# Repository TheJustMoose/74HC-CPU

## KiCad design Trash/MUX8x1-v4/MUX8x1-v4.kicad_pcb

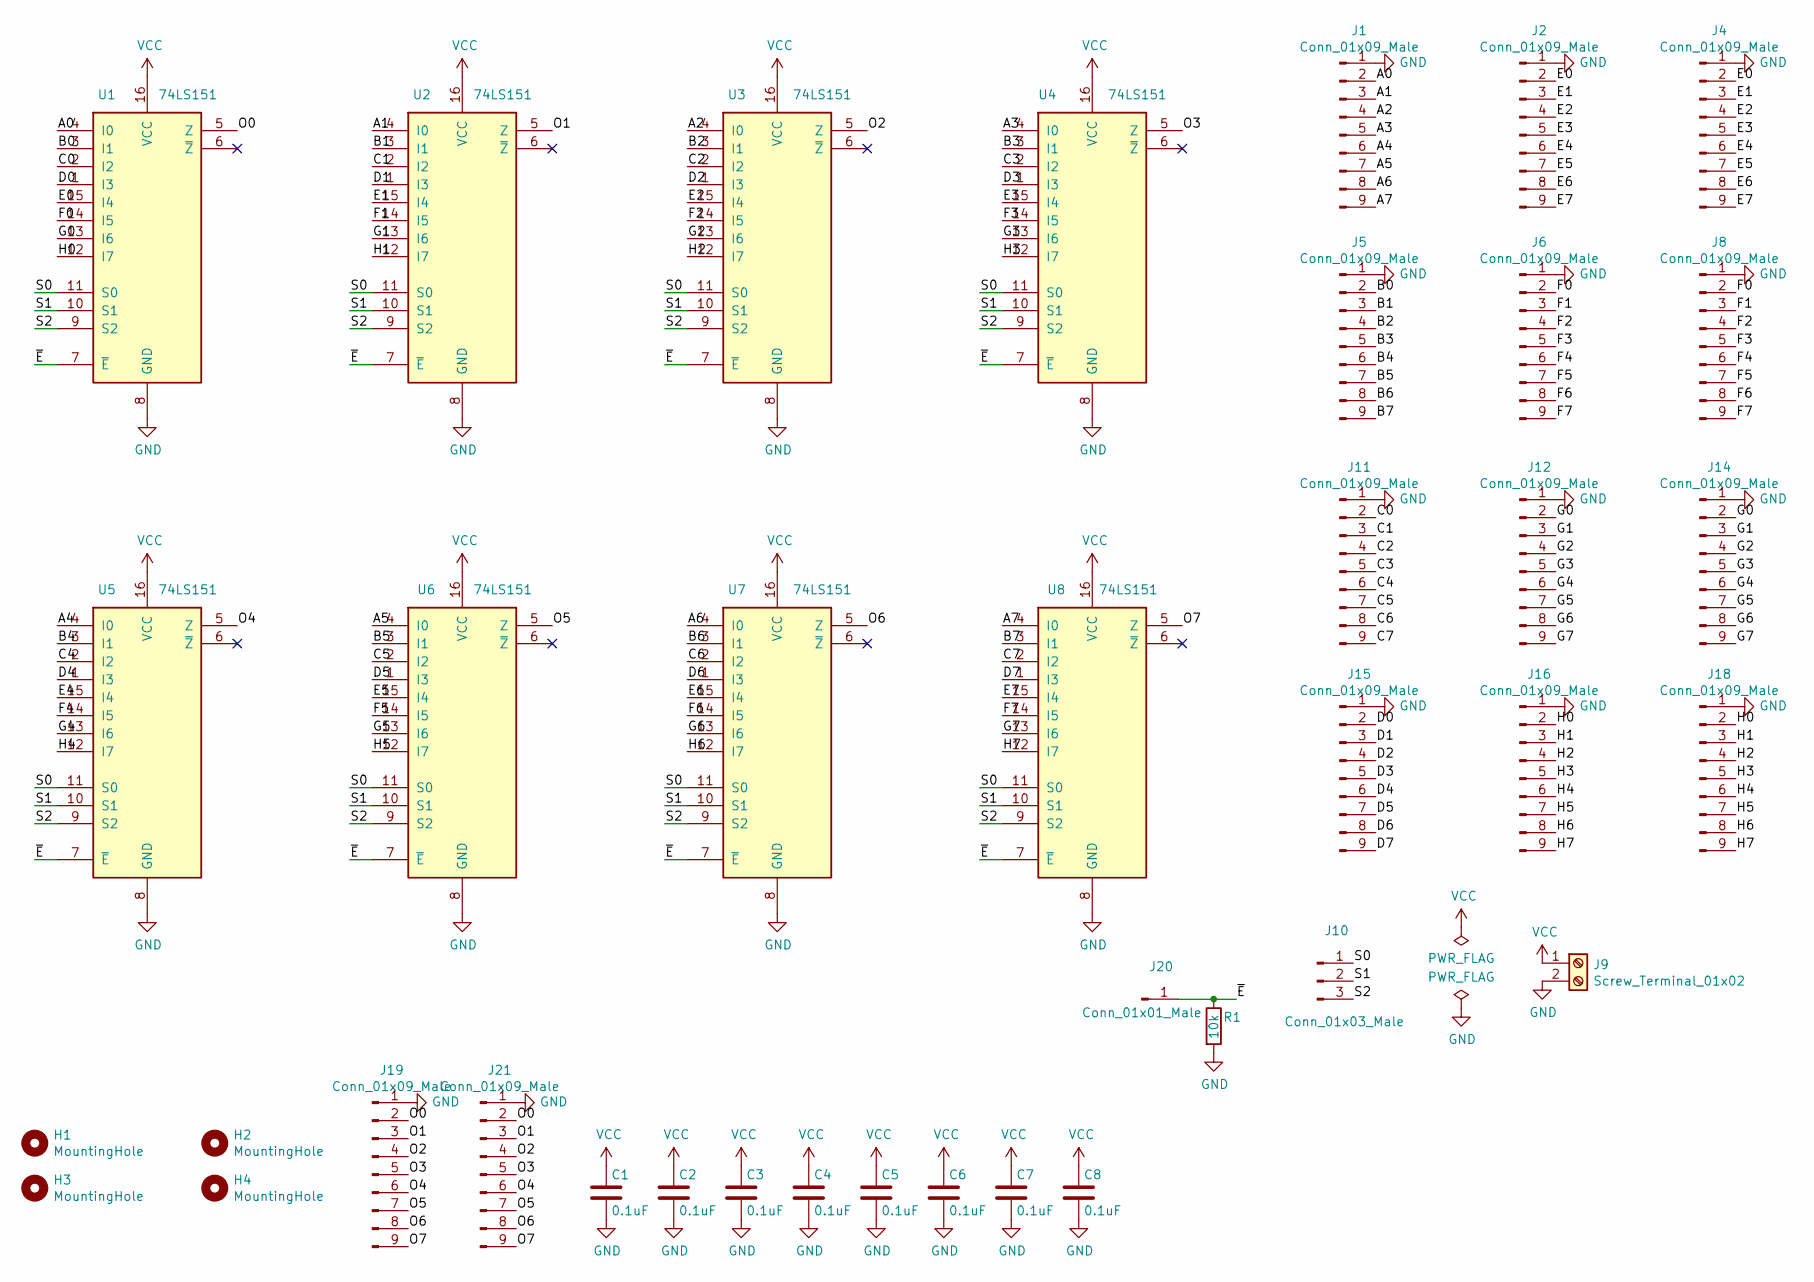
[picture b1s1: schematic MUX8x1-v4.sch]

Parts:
C1, C2, C3, C4, C5, C6, C7, C8: 0.1uF; C_Axial_L5.1mm_D3.1mm_P15.00mm_Horizontal
H1, H2, H3, H4: MountingHole; MountingHole_3.2mm_M3
J1, J2, J4, J5, J6, J8, J11, J12, J14, J15, J16, J18, J19, J21: Conn_01x09_Male; PinHeader_1x09_P2.54mm_Vertical
J9: Screw_Terminal_01x02; TerminalBlock_Phoenix_MKDS-1,5-2_1x02_P5.00mm_Horizontal
J10: Conn_01x03_Male; PinHeader_1x03_P2.54mm_Vertical
J20: Conn_01x01_Male; PinHeader_1x01_P2.54mm_Vertical
R1: 10k; R_0805_2012Metric_Pad1.20x1.40mm_HandSolder
U1, U2, U3, U4, U5, U6, U7, U8: 74LS151; DIP-16_W7.62mm_Socket

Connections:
/A0: J1.2, U1.4 (I0)
/A1: J1.3, U2.4 (I0)
/A2: J1.4, U3.4 (I0)
/A3: J1.5, U4.4 (I0)
/A4: J1.6, U5.4 (I0)
/A5: J1.7, U6.4 (I0)
/A6: J1.8, U7.4 (I0)
/A7: J1.9, U8.4 (I0)
/B0: J5.2, U1.3 (I1)
/B1: J5.3, U2.3 (I1)
/B2: J5.4, U3.3 (I1)
/B3: J5.5, U4.3 (I1)
/B4: J5.6, U5.3 (I1)
/B5: J5.7, U6.3 (I1)
/B6: J5.8, U7.3 (I1)
/B7: J5.9, U8.3 (I1)
/C0: J11.2, U1.2 (I2)
/C1: J11.3, U2.2 (I2)
/C2: J11.4, U3.2 (I2)
/C3: J11.5, U4.2 (I2)
/C4: J11.6, U5.2 (I2)
/C5: J11.7, U6.2 (I2)
/C6: J11.8, U7.2 (I2)
/C7: J11.9, U8.2 (I2)
/D0: J15.2, U1.1 (I3)
/D1: J15.3, U2.1 (I3)
/D2: J15.4, U3.1 (I3)
/D3: J15.5, U4.1 (I3)
/D4: J15.6, U5.1 (I3)
/D5: J15.7, U6.1 (I3)
/D6: J15.8, U7.1 (I3)
/D7: J15.9, U8.1 (I3)
/E0: J2.2, J4.2, U1.15 (I4)
/E1: J2.3, J4.3, U2.15 (I4)
/E2: J2.4, J4.4, U3.15 (I4)
/E3: J2.5, J4.5, U4.15 (I4)
/E4: J2.6, J4.6, U5.15 (I4)
/E5: J2.7, J4.7, U6.15 (I4)
/E6: J2.8, J4.8, U7.15 (I4)
/E7: J2.9, J4.9, U8.15 (I4)
/F0: J6.2, J8.2, U1.14 (I5)
/F1: J6.3, J8.3, U2.14 (I5)
/F2: J6.4, J8.4, U3.14 (I5)
/F3: J6.5, J8.5, U4.14 (I5)
/F4: J6.6, J8.6, U5.14 (I5)
/F5: J6.7, J8.7, U6.14 (I5)
/F6: J6.8, J8.8, U7.14 (I5)
/F7: J6.9, J8.9, U8.14 (I5)
/G0: J12.2, J14.2, U1.13 (I6)
/G1: J12.3, J14.3, U2.13 (I6)
/G2: J12.4, J14.4, U3.13 (I6)
/G3: J12.5, J14.5, U4.13 (I6)
/G4: J12.6, J14.6, U5.13 (I6)
/G5: J12.7, J14.7, U6.13 (I6)
/G6: J12.8, J14.8, U7.13 (I6)
/G7: J12.9, J14.9, U8.13 (I6)
/H0: J16.2, J18.2, U1.12 (I7)
/H1: J16.3, J18.3, U2.12 (I7)
/H2: J16.4, J18.4, U3.12 (I7)
/H3: J16.5, J18.5, U4.12 (I7)
/H4: J16.6, J18.6, U5.12 (I7)
/H5: J16.7, J18.7, U6.12 (I7)
/H6: J16.8, J18.8, U7.12 (I7)
/H7: J16.9, J18.9, U8.12 (I7)
/O0: J19.2, J21.2, U1.5 (Z)
/O1: J19.3, J21.3, U2.5 (Z)
/O2: J19.4, J21.4, U3.5 (Z)
/O3: J19.5, J21.5, U4.5 (Z)
/O4: J19.6, J21.6, U5.5 (Z)
/O5: J19.7, J21.7, U6.5 (Z)
/O6: J19.8, J21.8, U7.5 (Z)
/O7: J19.9, J21.9, U8.5 (Z)
/S0: J10.1, U1.11 (S0), U2.11 (S0), U3.11 (S0), U4.11 (S0), U5.11 (S0), U6.11 (S0), U7.11 (S0), U8.11 (S0)
/S1: J10.2, U1.10 (S1), U2.10 (S1), U3.10 (S1), U4.10 (S1), U5.10 (S1), U6.10 (S1), U7.10 (S1), U8.10 (S1)
/S2: J10.3, U1.9 (S2), U2.9 (S2), U3.9 (S2), U4.9 (S2), U5.9 (S2), U6.9 (S2), U7.9 (S2), U8.9 (S2)
/~E: J20.1, R1.1, U1.7 (~E), U2.7 (~E), U3.7 (~E), U4.7 (~E), U5.7 (~E), U6.7 (~E), U7.7 (~E), U8.7 (~E)
GND: C1.2, C2.2, C3.2, C4.2, C5.2, C6.2, C7.2, C8.2, J1.1, J2.1, J4.1, J5.1, J6.1, J8.1, J9.2, J11.1, J12.1, J14.1, J15.1, J16.1, J18.1, J19.1, J21.1, R1.2, U1.8 (GND), U2.8 (GND), U3.8 (GND), U4.8 (GND), U5.8 (GND), U6.8 (GND), U7.8 (GND), U8.8 (GND)
VCC: C1.1, C2.1, C3.1, C4.1, C5.1, C6.1, C7.1, C8.1, J9.1, U1.16 (VCC), U2.16 (VCC), U3.16 (VCC), U4.16 (VCC), U5.16 (VCC), U6.16 (VCC), U7.16 (VCC), U8.16 (VCC)

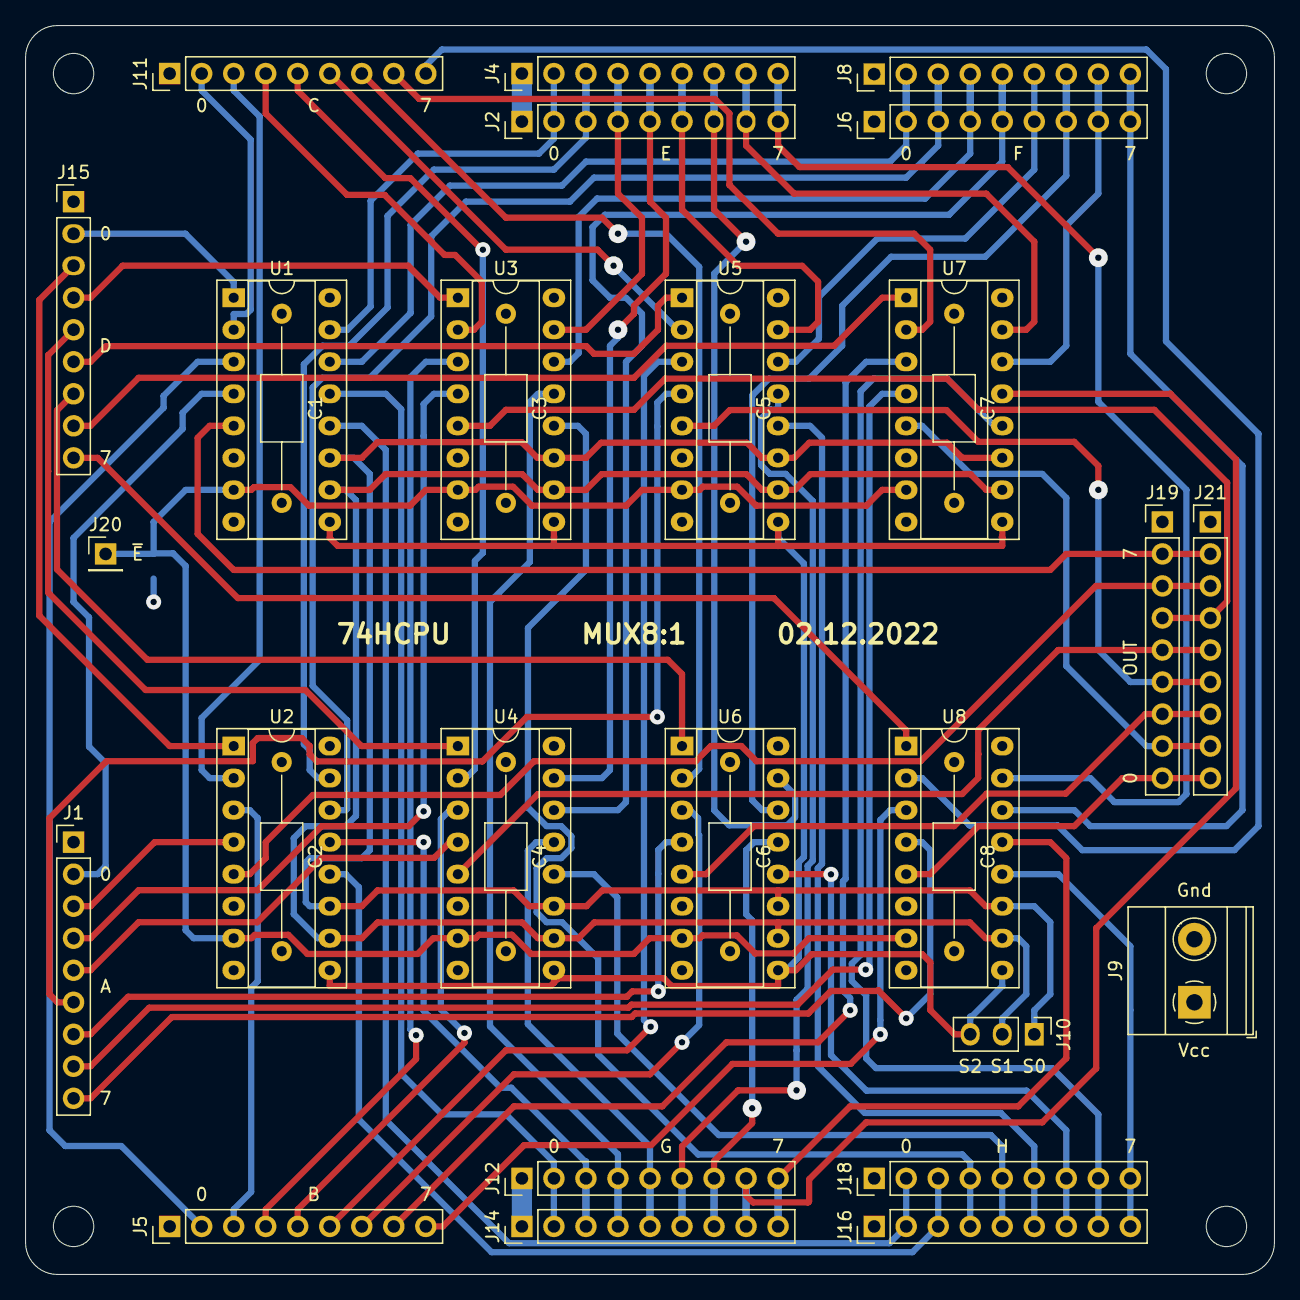
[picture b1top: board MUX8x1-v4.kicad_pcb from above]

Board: 4 copper layers, 99.1 x 99.1 mm, 38 parts (1 on the bottom side), 78 nets.

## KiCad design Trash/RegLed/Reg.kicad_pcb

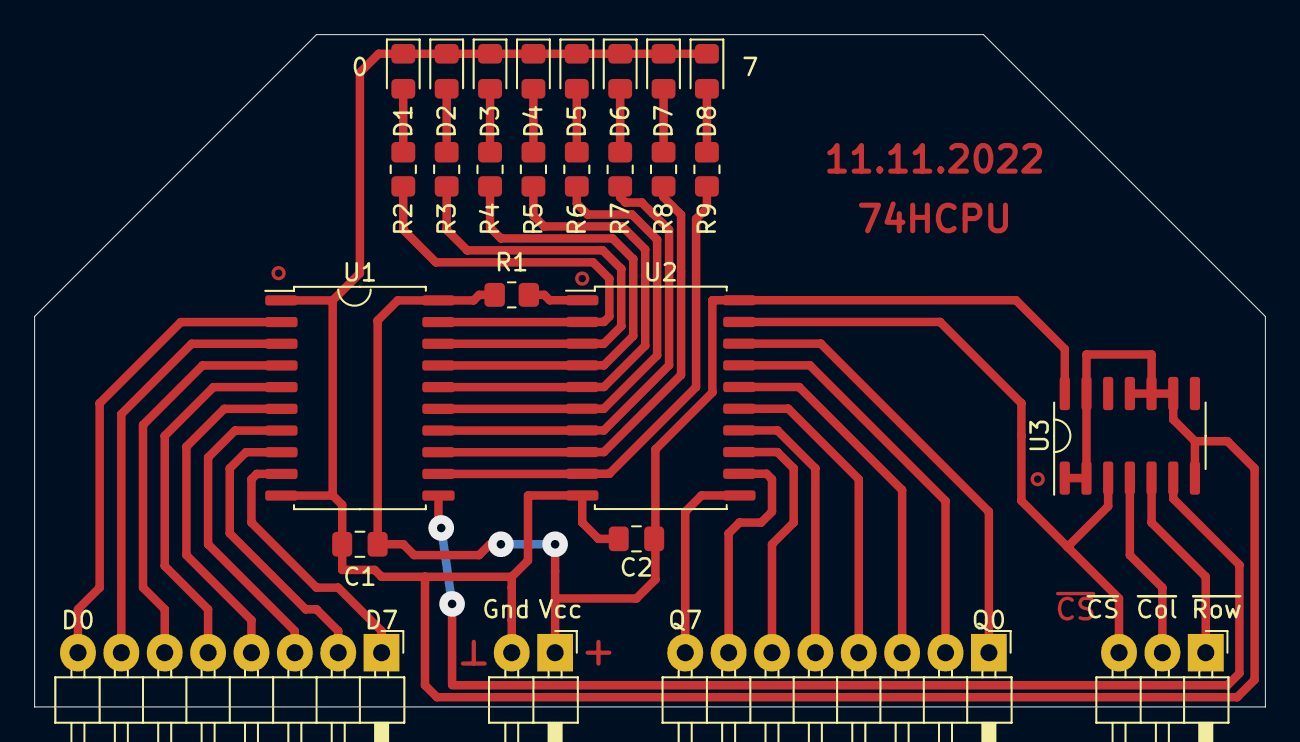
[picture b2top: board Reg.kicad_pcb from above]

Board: 2 copper layers, 72.1 x 39.4 mm, 26 parts (0 on the bottom side), 39 nets.

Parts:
C1, C2: 0.1uF; C_0805_2012Metric_Pad1.18x1.45mm_HandSolder
D1, D2, D3, D4, D5, D6, D7, D8: LED; LED_0805_2012Metric_Pad1.15x1.40mm_HandSolder
J1, J2: Conn_01x08_Male; PinHeader_1x08_P2.54mm_Horizontal
J3: Conn_01x02_Male; PinHeader_1x02_P2.54mm_Horizontal
J4: Conn_01x03_Male; PinHeader_1x03_P2.54mm_Horizontal
R1: 10k; R_0805_2012Metric_Pad1.20x1.40mm_HandSolder
R2, R3, R4, R5, R6, R7, R8, R9: 1k; R_0805_2012Metric_Pad1.20x1.40mm_HandSolder
U1: 74LS573; SOP-20_7.5x12.8mm_P1.27mm
U2: 74HC245; SOP-20_7.5x12.8mm_P1.27mm
U3: 74LS27; SO-14_3.9x8.65mm_P1.27mm

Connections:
/D0: J1.8, U1.2
/D1: J1.7, U1.3
/D2: J1.6, U1.4
/D3: J1.5, U1.5
/D4: J1.4, U1.6
/D5: J1.3, U1.7
/D6: J1.2, U1.8
/D7: J1.1, U1.9
/L0: R2.1, U1.19, U2.2
/L1: R3.1, U1.18, U2.3
/L2: R4.1, U1.17, U2.4
/L3: R5.1, U1.16, U2.5
/L4: R6.1, U1.15, U2.6
/L5: R7.1, U1.14, U2.7
/L6: R8.1, U1.13, U2.8
/L7: R9.1, U1.12, U2.9
/Q0: J2.1, U2.18
/Q1: J2.2, U2.17
/Q2: J2.3, U2.16
/Q3: J2.4, U2.15
/Q4: J2.5, U2.14
/Q5: J2.6, U2.13
/Q6: J2.7, U2.12
/Q7: J2.8, U2.11
/~CS: J4.3, U2.19, U3.3
/~Col: J4.2, U3.4
/~Row: J4.1, U3.5
GND: C1.2, C2.2, D1.1, D2.1, D3.1, D4.1, D5.1, D6.1, D7.1, D8.1, J3.2, U1.1, U1.10, U2.10, U3.1, U3.2, U3.7, U3.9, U3.10, U3.11, U3.13
unnamed: D1.2, R2.2
unnamed: D2.2, R3.2
unnamed: D3.2, R4.2
unnamed: D4.2, R5.2
unnamed: D5.2, R6.2
unnamed: D6.2, R7.2
unnamed: D7.2, R8.2
unnamed: D8.2, R9.2
unnamed: R1.1, U2.1
unnamed: U1.11, U3.6
VCC: C1.1, C2.1, J3.1, R1.2, U1.20, U2.20, U3.14

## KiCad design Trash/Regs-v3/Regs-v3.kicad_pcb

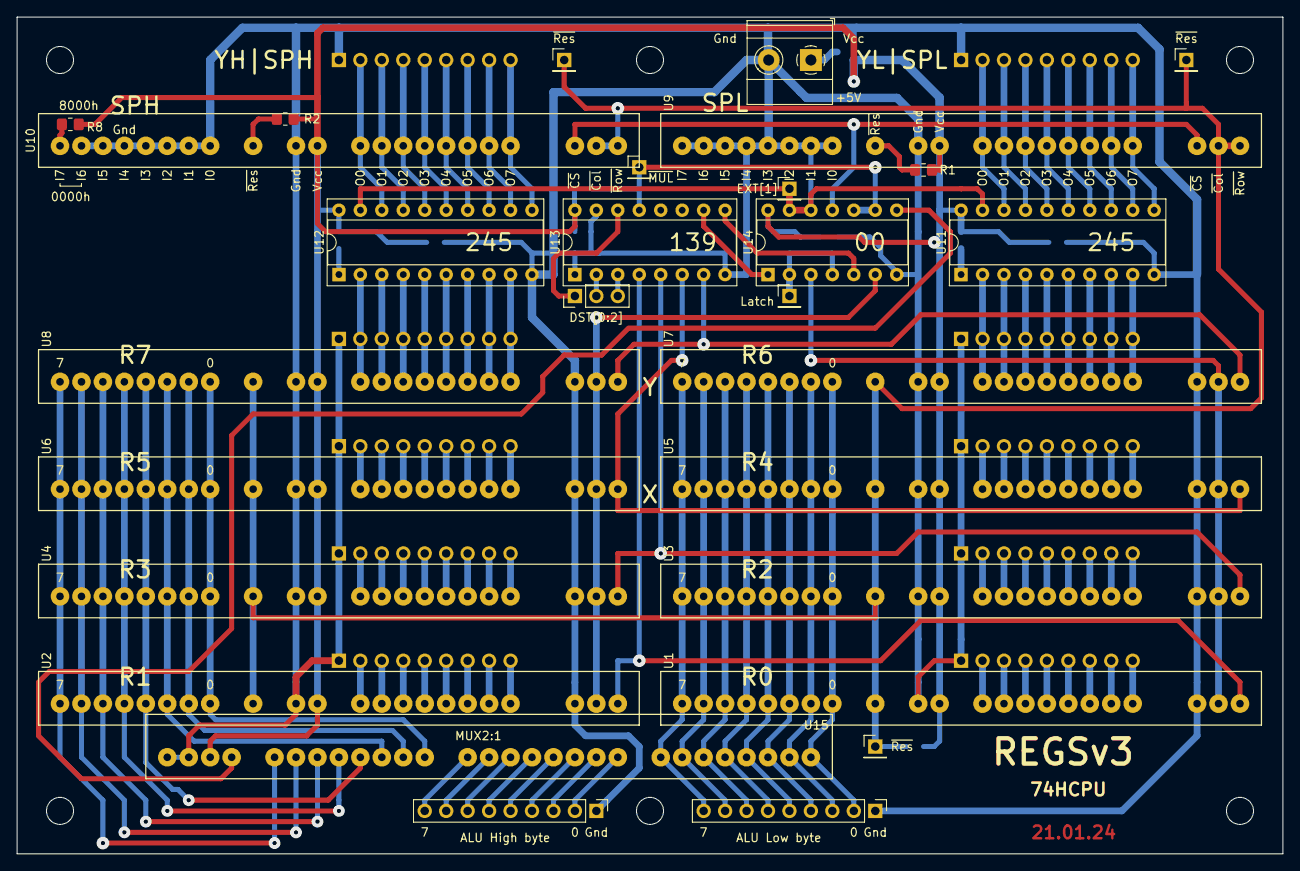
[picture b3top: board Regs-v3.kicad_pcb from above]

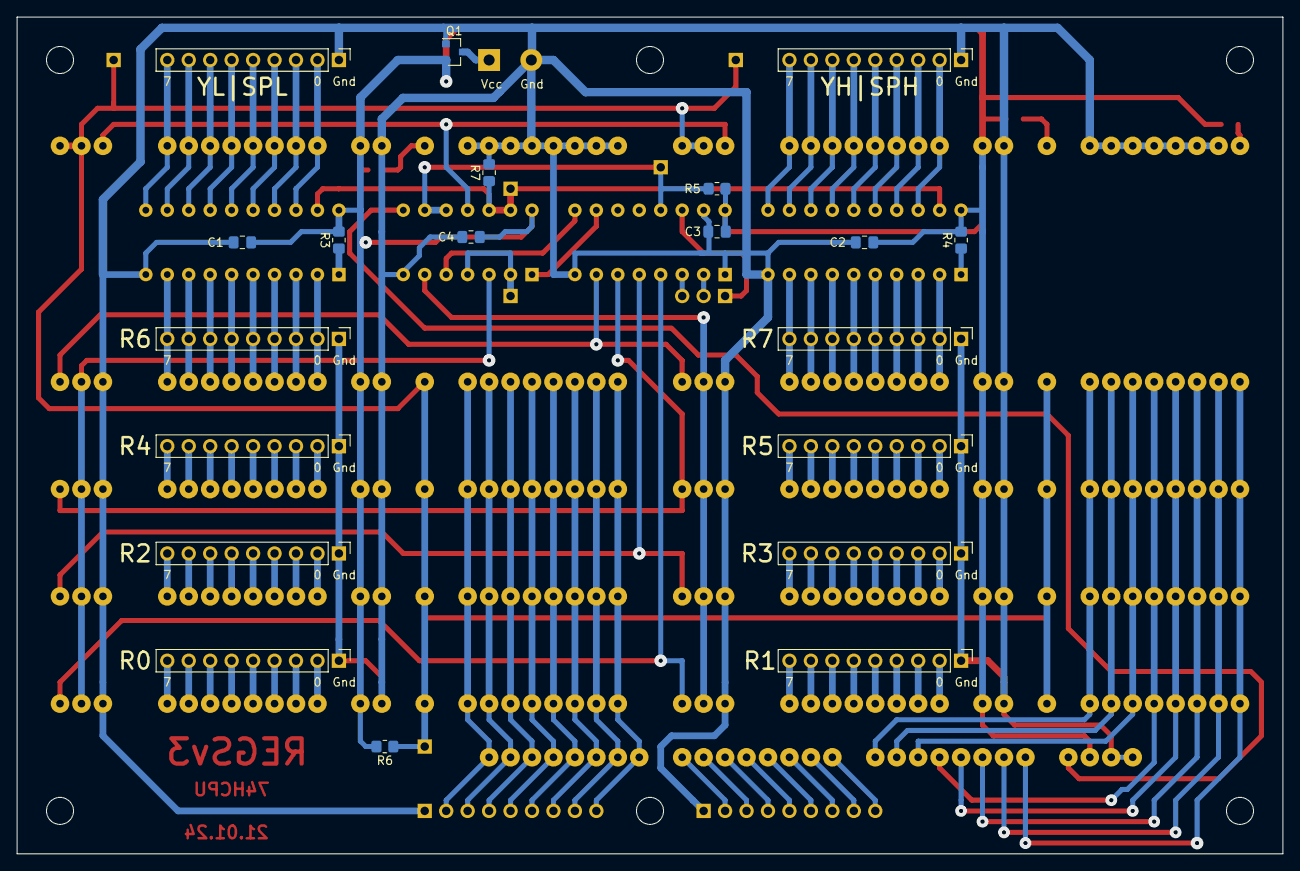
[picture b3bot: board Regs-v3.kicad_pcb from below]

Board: 2 copper layers, 149.9 x 99.1 mm, 54 parts (20 on the bottom side), 129 nets.

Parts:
C1, C2, C3, C4: 0.1uF; C_0805_2012Metric_Pad1.18x1.45mm_HandSolder
H1, H2, H3, H4, H5, H6: MountingHole; MountingHole_3.2mm_M3
J1, J2, J3, J4, J5, J6, J7, J8, J9, J10, J17, J18: Conn_01x09_Male; PinHeader_1x09_P2.54mm_Vertical
J11: Conn_01x03_Male; PinHeader_1x03_P2.54mm_Vertical
J12, J13, J14, J15, J19, J20: Conn_01x01_Male; PinHeader_1x01_P2.54mm_Vertical
J16: Screw_Terminal_01x02; TerminalBlock_Phoenix_MKDS-1,5-2_1x02_P5.00mm_Horizontal
Q1: IRLML5203; SOT-23
R1, R2, R3, R4, R5, R6, R7, R8: 10k; R_0805_2012Metric_Pad1.20x1.40mm_HandSolder
U1, U2, U3, U4, U5, U6, U7, U8, U9, U10: REG_CNT
U11, U12: 74HC245; DIP-20_W7.62mm_Socket
U13: 74LS139; DIP-16_W7.62mm_Socket
U14: 74HC00; DIP-14_W7.62mm_Socket
U15: MUX2-1; CMDwoC

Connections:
/ALU_H0: J18.2, U15.9
/ALU_H7: J18.9, U15.16
/DST[0]: J11.1, U13.14
/DST[1]: J11.2, U13.2
/DST[2]: J11.3, U13.3
/EXT[1]: J14.1, R7.1, U11.19, U12.19, U14.12, U14.13
/H0: U2.8, U4.8, U6.8, U8.8, U15.17
/H1: U2.7, U4.7, U6.7, U8.7, U15.18
/H2: U2.6, U4.6, U6.6, U8.6, U15.19
/H3: U2.5, U4.5, U6.5, U8.5, U15.20
/H4: U2.4, U4.4, U6.4, U8.4, U15.21
/H5: U2.3, U4.3, U6.3, U8.3, U15.22
/H6: U2.2, U4.2, U6.2, U8.2, U15.23
/H7: U2.1, U4.1, U6.1, U8.1, U15.24
/L0: J17.2, U1.8, U3.8, U5.8, U7.8, U15.1
/L1: J17.3, U1.7, U3.7, U5.7, U7.7, U15.2
/L2: J17.4, U1.6, U3.6, U5.6, U7.6, U15.3
/L3: J17.5, U1.5, U3.5, U5.5, U7.5, U15.4
/L4: J17.6, U1.4, U3.4, U5.4, U7.4, U15.5
/L5: J17.7, U1.3, U3.3, U5.3, U7.3, U15.6
/L6: J17.8, U1.2, U3.2, U5.2, U7.2, U15.7
/L7: J17.9, U1.1, U3.1, U5.1, U7.1, U15.8
/Latch: J15.1, U14.2, U14.4
/R0.0: J1.2, U1.12
/R0.1: J1.3, U1.13
/R0.2: J1.4, U1.14
/R0.3: J1.5, U1.15
/R0.4: J1.6, U1.16
/R0.5: J1.7, U1.17
/R0.6: J1.8, U1.18
/R0.7: J1.9, U1.19
/R1.0: J2.2, U2.12
/R1.1: J2.3, U2.13
/R1.2: J2.4, U2.14
/R1.3: J2.5, U2.15
/R1.4: J2.6, U2.16
/R1.5: J2.7, U2.17
/R1.6: J2.8, U2.18
/R1.7: J2.9, U2.19
/R2.0: J3.2, U3.12
/R2.1: J3.3, U3.13
/R2.2: J3.4, U3.14
/R2.3: J3.5, U3.15
/R2.4: J3.6, U3.16
/R2.5: J3.7, U3.17
/R2.6: J3.8, U3.18
/R2.7: J3.9, U3.19
/R3.0: J4.2, U4.12
/R3.1: J4.3, U4.13
/R3.2: J4.4, U4.14
/R3.3: J4.5, U4.15
/R3.4: J4.6, U4.16
/R3.5: J4.7, U4.17
/R3.6: J4.8, U4.18
/R3.7: J4.9, U4.19
/R4.0: J5.2, U5.12
/R4.1: J5.3, U5.13
/R4.2: J5.4, U5.14
/R4.3: J5.5, U5.15
/R4.4: J5.6, U5.16
/R4.5: J5.7, U5.17
/R4.6: J5.8, U5.18
/R4.7: J5.9, U5.19
/R5.0: J6.2, U6.12
/R5.1: J6.3, U6.13
/R5.2: J6.4, U6.14
/R5.3: J6.5, U6.15
/R5.4: J6.6, U6.16
/R5.5: J6.7, U6.17
/R5.6: J6.8, U6.18
/R5.7: J6.9, U6.19
/R6.0: J7.2, U7.12, U11.2
/R6.1: J7.3, U7.13, U11.3
/R6.2: J7.4, U7.14, U11.4
/R6.3: J7.5, U7.15, U11.5
/R6.4: J7.6, U7.16, U11.6
/R6.5: J7.7, U7.17, U11.7
/R6.6: J7.8, U7.18, U11.8
/R6.7: J7.9, U7.19, U11.9
/R7.0: J8.2, U8.12, U12.2
/R7.1: J8.3, U8.13, U12.3
/R7.2: J8.4, U8.14, U12.4
/R7.3: J8.5, U8.15, U12.5
/R7.4: J8.6, U8.16, U12.6
/R7.5: J8.7, U8.17, U12.7
/R7.6: J8.8, U8.18, U12.8
/R7.7: J8.9, U8.19, U12.9
/YH|SPH.0: J10.2, U10.12, U12.18
/YH|SPH.1: J10.3, U10.13, U12.17
/YH|SPH.2: J10.4, U10.14, U12.16
/YH|SPH.3: J10.5, U10.15, U12.15
/YH|SPH.4: J10.6, U10.16, U12.14
/YH|SPH.5: J10.7, U10.17, U12.13
/YH|SPH.6: J10.8, U10.18, U12.12
/YH|SPH.7: J10.9, U10.19, U12.11
/YL|SPL.0: J9.2, U9.12, U11.18
/YL|SPL.1: J9.3, U9.13, U11.17
/YL|SPL.2: J9.4, U9.14, U11.16
/YL|SPL.3: J9.5, U9.15, U11.15
/YL|SPL.4: J9.6, U9.16, U11.14
/YL|SPL.5: J9.7, U9.17, U11.13
/YL|SPL.6: J9.8, U9.18, U11.12
/YL|SPL.7: J9.9, U9.19, U11.11
/~H: U2.21, U4.21, U6.21, U8.21, U14.6
/~L: U1.21, U3.21, U5.21, U7.21, U14.3
/~MUL: J12.1, R5.1, U13.13, U14.9, U14.10
/~R0: U1.22, U2.22, U13.4
/~R1: U3.22, U4.22, U13.5
/~R2: U5.22, U6.22, U13.6
/~R3: U7.22, U8.22, U13.7
/~Res: J13.1, J19.1, J20.1, R6.1, U1.9, U2.9, U3.9, U4.9, U5.9, U6.9, U7.9, U8.9, U9.21, U9.22, U10.21, U10.22
GND: C1.2, C2.2, C3.2, C4.2, J1.1, J2.1, J3.1, J4.1, J5.1, J6.1, J7.1, J8.1, J9.1, J10.1, J16.2, J17.1, J18.1, Q1.1, R7.2, U1.10, U1.20, U2.10, U2.20, U3.10, U3.20, U4.10, U4.20, U5.10, U5.20, U6.10, U6.20, U7.10, U7.20, U8.10, U8.20, U9.1, U9.2, U9.3, U9.4, U9.5, U9.6, U9.7, U9.8, U9.10, U10.2, U10.3, U10.4, U10.5, U10.6, U10.7, U10.8, U10.10, U11.10, U12.10, U13.1, U13.8, U13.15, U14.7, U15.27, U15.28
unnamed: J16.1, Q1.3
unnamed: J18.3, U15.10
unnamed: J18.4, U15.11
unnamed: J18.5, U15.12
unnamed: J18.6, U15.13
unnamed: J18.7, U15.14
unnamed: J18.8, U15.15
unnamed: R1.1, U9.9
unnamed: R2.1, U10.9
unnamed: R3.1, U11.1
unnamed: R4.1, U12.1
unnamed: R8.1, U10.1
unnamed: U9.20, U10.20, U14.11
unnamed: U13.9, U14.5
unnamed: U13.10, U14.1
unnamed: U14.8, U15.25
VCC: C1.1, C2.1, C3.1, C4.1, Q1.2, R1.2, R2.2, R3.2, R4.2, R5.2, R6.2, R8.2, U1.11, U2.11, U3.11, U4.11, U5.11, U6.11, U7.11, U8.11, U9.11, U10.11, U11.20, U12.20, U13.16, U14.14, U15.26

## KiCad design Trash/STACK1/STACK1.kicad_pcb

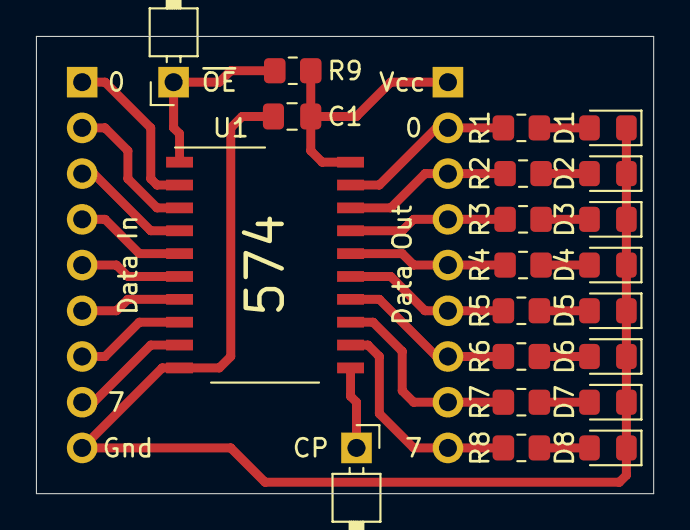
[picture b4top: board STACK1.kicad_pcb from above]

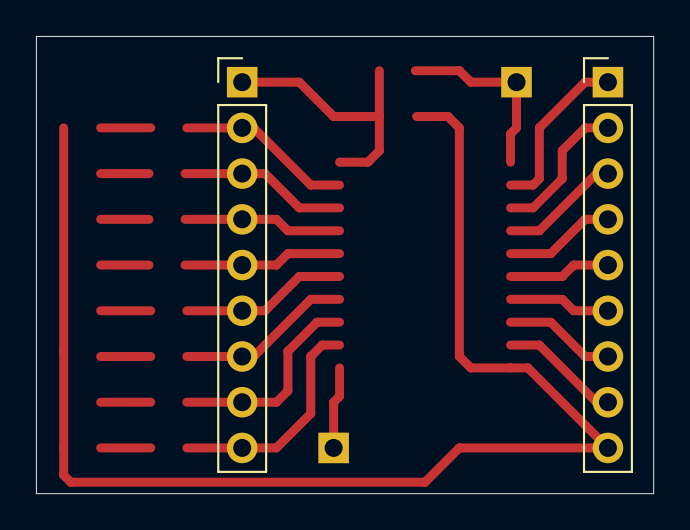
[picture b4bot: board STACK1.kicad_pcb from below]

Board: 2 copper layers, 34.3 x 25.4 mm, 23 parts (2 on the bottom side), 28 nets.

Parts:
C1: 0.1uF; C_0805_2012Metric_Pad1.18x1.45mm_HandSolder
D1, D2, D3, D4, D5, D6, D7, D8: LED; LED_0805_2012Metric_Pad1.15x1.40mm_HandSolder
J1, J2: Conn_01x09_Male; PinHeader_1x09_P2.54mm_Vertical
J3, J4: Conn_01x01_Male; PinHeader_1x01_P2.54mm_Horizontal
R1, R2, R3, R4, R5, R6, R7, R8: 1k; R_0805_2012Metric_Pad1.20x1.40mm_HandSolder
R9: 10k; R_0805_2012Metric_Pad1.20x1.40mm_HandSolder
U1: 74LS574; SO-20_12.8x7.5mm_P1.27mm

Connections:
/CP: J3.1, U1.11
/D0: J2.1, U1.2
/D7: J2.8, U1.9
/Q0: J1.2, R1.2, U1.19
/Q1: J1.3, R2.2, U1.18
/Q2: J1.4, R3.2, U1.17
/Q3: J1.5, R4.2, U1.16
/Q4: J1.6, R5.2, U1.15
/Q5: J1.7, R6.2, U1.14
/Q6: J1.8, R7.2, U1.13
/Q7: J1.9, R8.2, U1.12
/~OE: J4.1, R9.1, U1.1
GND: C1.2, D1.1, D2.1, D3.1, D4.1, D5.1, D6.1, D7.1, D8.1, J2.9, U1.10
unnamed: D1.2, R1.1
unnamed: D2.2, R2.1
unnamed: D3.2, R3.1
unnamed: D4.2, R4.1
unnamed: D5.2, R5.1
unnamed: D6.2, R6.1
unnamed: D7.2, R7.1
unnamed: D8.2, R8.1
unnamed: J2.2, U1.3
unnamed: J2.3, U1.4
unnamed: J2.4, U1.5
unnamed: J2.5, U1.6
unnamed: J2.6, U1.7
unnamed: J2.7, U1.8
VCC: C1.1, J1.1, R9.2, U1.20

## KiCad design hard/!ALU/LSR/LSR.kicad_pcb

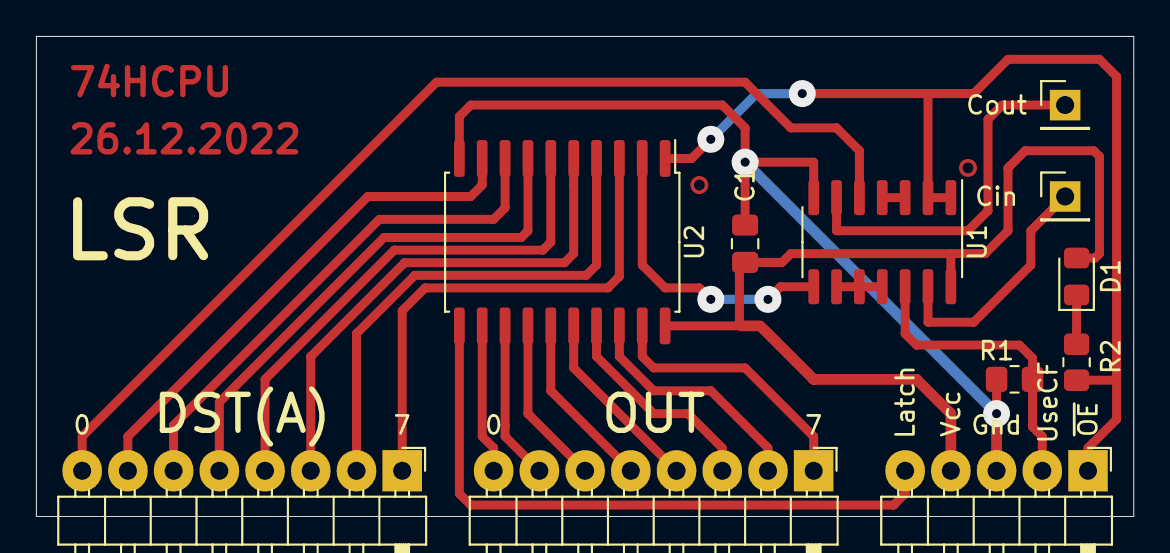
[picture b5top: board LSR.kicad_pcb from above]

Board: 2 copper layers, 61.0 x 26.7 mm, 11 parts (0 on the bottom side), 27 nets.

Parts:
C1: 0.1uF; C_0805_2012Metric_Pad1.18x1.45mm_HandSolder
D1: LED; LED_0805_2012Metric_Pad1.15x1.40mm_HandSolder
J1, J4: Conn_01x01_Male; PinHeader_1x01_P2.54mm_Vertical
J2, J3: Conn_01x08_Male; PinHeader_1x08_P2.54mm_Horizontal
J5: Conn_01x05_Male; PinHeader_1x05_P2.54mm_Horizontal
R1, R2: R; R_0805_2012Metric_Pad1.20x1.40mm_HandSolder
U1: 74HC00; SO-14_3.9x8.65mm_P1.27mm
U2: 74LS573; SOIC-20W_7.5x12.8mm_P1.27mm

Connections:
/CF_IN: J4.1, U1.13
/D0: J2.8, U1.5
/D1: J2.7, U2.9
/D2: J2.6, U2.8
/D3: J2.5, U2.7
/D4: J2.4, U2.6
/D5: J2.3, U2.5
/D6: J2.2, U2.4
/D7: J2.1, U2.3
/Latch: J5.5, U2.11
/O0: J3.8, U2.12
/O1: J3.7, U2.13
/O2: J3.6, U2.14
/O3: J3.5, U2.15
/O4: J3.4, U2.16
/O5: J3.3, U2.17
/O6: J3.2, U2.18
/O7: J3.1, U2.19
/UseCF: J5.2, R1.1, U1.12
/~(CF&OE): J1.1, U1.6
/~OE: J5.1, R2.2, U1.1, U1.2, U2.1
GND: C1.2, J5.3, R1.2, U1.7, U2.10
unnamed: D1.1, R2.1
unnamed: U1.3, U1.4
unnamed: U1.8, U2.2
unnamed: U1.9, U1.10, U1.11
VCC: C1.1, D1.2, J5.4, U1.14, U2.20

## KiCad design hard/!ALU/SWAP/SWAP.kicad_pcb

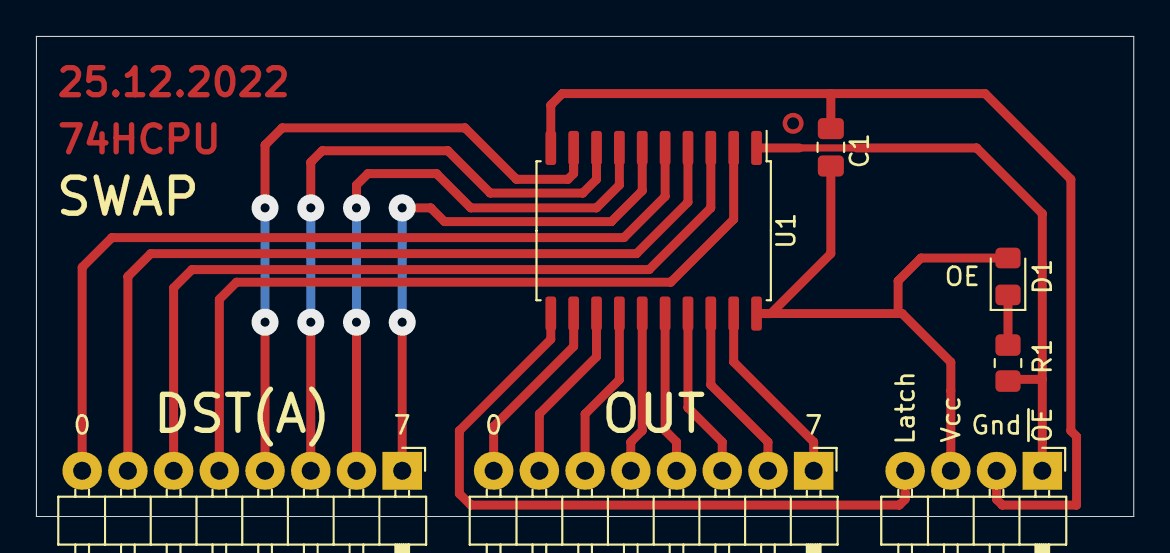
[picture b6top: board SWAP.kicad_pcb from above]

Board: 2 copper layers, 61.0 x 26.7 mm, 7 parts (0 on the bottom side), 21 nets.

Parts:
C1: 0.1uF; C_0805_2012Metric_Pad1.18x1.45mm_HandSolder
D1: LED; LED_0805_2012Metric_Pad1.15x1.40mm_HandSolder
J2, J3: Conn_01x08_Male; PinHeader_1x08_P2.54mm_Horizontal
J4: Conn_01x04_Male; PinHeader_1x04_P2.54mm_Horizontal
R1: 1k; R_0805_2012Metric_Pad1.20x1.40mm_HandSolder
U1: 74LS573; SOP-20_7.5x12.8mm_P1.27mm

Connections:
/A0: J2.8, U1.5
/A1: J2.7, U1.4
/A2: J2.6, U1.3
/A3: J2.5, U1.2
/A4: J2.4, U1.9
/A5: J2.3, U1.8
/A6: J2.2, U1.7
/A7: J2.1, U1.6
/Latch: J4.4, U1.11
/OUT0: J3.8, U1.12
/OUT7: J3.1, U1.19
/~OE: J4.1, R1.2, U1.1
GND: C1.2, J4.2, U1.10
unnamed: D1.1, R1.1
unnamed: J3.2, U1.18
unnamed: J3.3, U1.17
unnamed: J3.4, U1.16
unnamed: J3.5, U1.15
unnamed: J3.6, U1.14
unnamed: J3.7, U1.13
VCC: C1.1, D1.2, J4.3, U1.20
